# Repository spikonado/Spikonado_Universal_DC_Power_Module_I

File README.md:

# Spikonado Universal DC Power Module I

The [Spikonado Universal DC Power Module I](https://spikonado.com/product/spikonado-universal-dc-power-module-i) is a versatile and high-current buck converter designed to power your most demanding electronics projects. It efficiently (92.7%) converts a wide **13-24** DC input into three stable, dedicated outputs:

- **12V @ 4A**
- **5V @ 10A**
- **3.3V @ 8A**

This module is perfect for robotics, embedded systems, single-board computers (SBCs), custom test jigs, and any application requiring reliable multi-voltage power.<br>
Further enhancing its flexibility, the board includes USB-C and USB-A outputs.<br>
What's more, we have also included EN and PG pins through which you can control the board using a microcontroller and also attach a switch to the board.

The board also includes the following protections:

1. Over Current Limit (OCL) - Protects the board from overloads by limiting the output current.
2. Undervoltage Lockout (UVLO) - When the input voltage on VIN falls below the required voltage, the particular voltage output shuts off.
3. Thermal Shutdown - When any of the buck converter ICs included on the board get too hot, the particular voltage output shuts off.
4. Undervoltage and Overvoltage Protection (UVP & OVP) (Not included for 12V output) - When the output voltage falls too low or goes too high than the desired voltage, the output is discharged and latched.

## 📂 About this Repository

This repository is your central hub for all information, design files, and resources related to the Spikonado Universal DC Power Module I. Our aim is to provide everything you need to understand, use, and even build upon this product.

You'll find:

- `docs/`: Comprehensive documentation, including datasheets, specifications, and user guides.
- `hardware_design/`: Complete KiCad project design files – schematics and PCB layout for the board.

## Accessing the Documentation

The `docs/` directory contains the source files for our comprehensive product documentation. For the best reading experience, with all formatting and interactive elements correctly rendered, please view the built version on our [website](https://docs.spikonado.com/Spikonado_Universal_DC_Power_Module_I).

While you can browse the raw files in the `docs/` directory on GitHub, they are primarily intended for those contributing to the documentation or exploring its source structure.

## 🤝 Contributing

Contributions, issues, and feature requests are welcome! Feel free to check existing issues or open a new one.

## 📄 License

This product is open source!

Please review the following files for license information:

- `hardware_design/LICENSE.md`

If you have any questions or concerns related to licensing, please email support at support@spikonado.com.

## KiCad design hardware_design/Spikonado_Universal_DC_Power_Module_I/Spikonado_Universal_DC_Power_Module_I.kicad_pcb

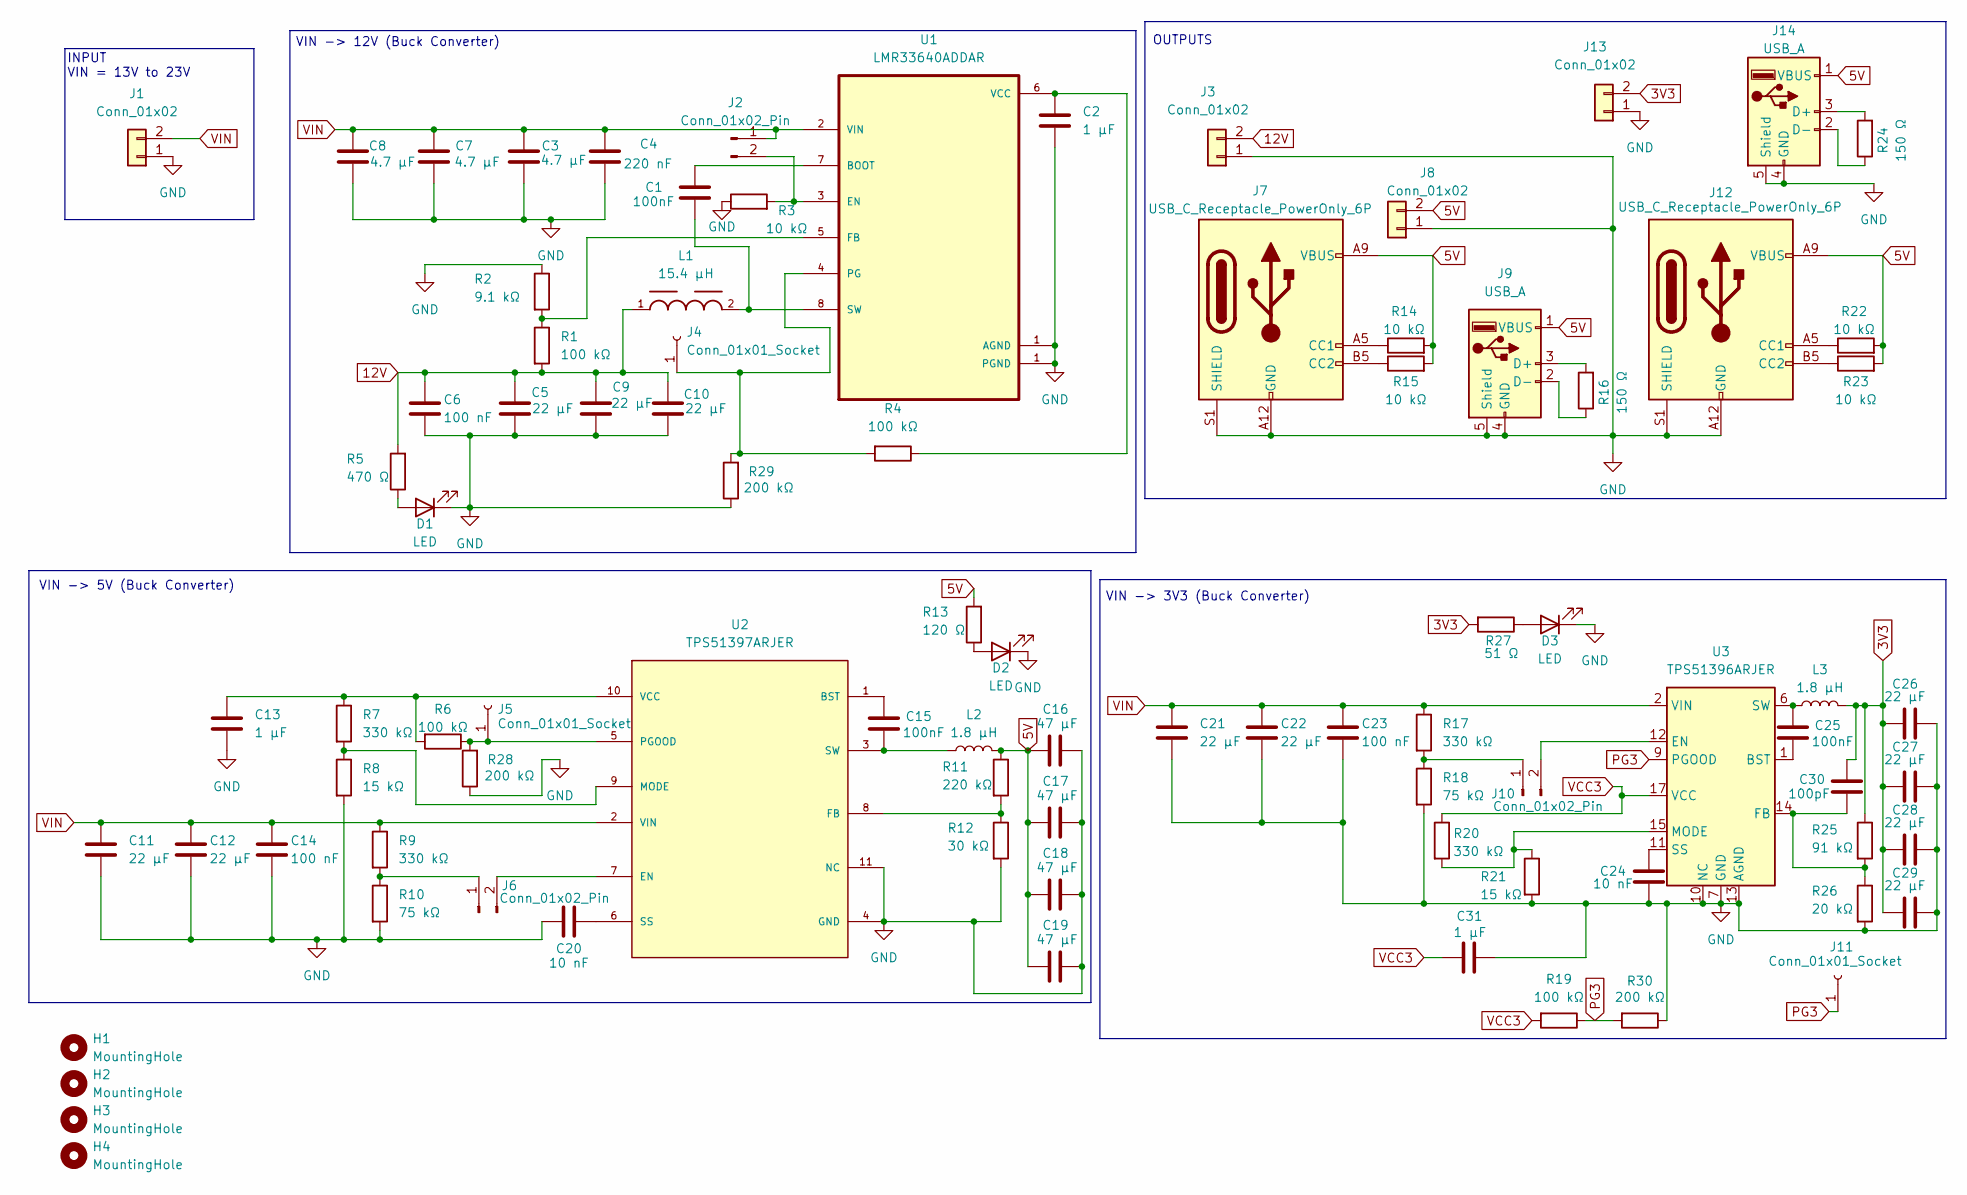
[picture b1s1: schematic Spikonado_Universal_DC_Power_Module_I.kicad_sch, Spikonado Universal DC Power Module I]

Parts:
C1, C15, C25: 100nF; C_0805_2012Metric
C2, C13, C31: 1 μF; C_0402_1005Metric
C3, C7, C8: 4.7 μF; C_1206_3216Metric
C4: 220 nF; C_0805_2012Metric
C5, C9, C10: 22 μF; C_0805_2012Metric
C6, C14, C23: 100 nF; C_0805_2012Metric
C11, C12, C21, C22, C26, C27, C28, C29: 22 μF; C_1206_3216Metric
C16, C17, C18, C19: 47 μF; C_1206_3216Metric
C20, C24: 10 nF; C_0805_2012Metric
C30: 100pF; C_0805_2012Metric
D1, D2, D3: LED; LED_0603_1608Metric
H1, H2, H3, H4: MountingHole; MountingHole_3.2mm_M3
J1, J3, J8, J13: Conn_01x02; TerminalBlock_MaiXu_MX126-5.0-02P_1x02_P5.00mm
J2, J6, J10: Conn_01x02_Pin; PinHeader_1x02_P2.54mm_Vertical
J4, J5, J11: Conn_01x01_Socket; PinSocket_1x01_P2.54mm_Vertical
J7, J12: USB_C_Receptacle_PowerOnly_6P; USB_C_Receptacle_GCT_USB4125-xx-x_6P_TopMnt_Horizontal
J9, J14: USB_A; USB_A_Connfly_DS1095
L1: 15.4 µH; WE-HCI_1365
L2, L3: 1.8 μH; IND_IHLP_5050_FD_VIS
R1, R4, R6, R19: 100 kΩ; R_0805_2012Metric
R2: 9.1 kΩ; C_0603_1608Metric
R3, R14, R15, R22, R23: 10 kΩ; R_0805_2012Metric
R5: 470 Ω; R_0805_2012Metric
R7, R9, R17, R20: 330 kΩ; R_0603_1608Metric
R8, R21: 15 kΩ; R_0603_1608Metric
R10, R18: 75 kΩ; R_0603_1608Metric
R11: 220 kΩ; R_0805_2012Metric
R12: 30 kΩ; R_0805_2012Metric
R13: 120 Ω; R_0805_2012Metric
R16, R24: 150 Ω; R_0805_2012Metric
R25: 91 kΩ; R_0603_1608Metric
R26: 20 kΩ; R_0603_1608Metric
R27: 51 Ω; R_0805_2012Metric
R28, R29, R30: 200 kΩ; R_0805_2012Metric
U1: LMR33640ADDAR; VREG_LM5017MR_NOPB
U2: TPS51397ARJER; RJE0020B-MFG
U3: TPS51396ARJER; Texas_RJE0020A_VQFN-20-1EP_3x3mm_P0.45mm_EP0.675x0.76mm_The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

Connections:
3V3: C26.2, C27.2, C28.2, C29.2, C30.1, J13.2, L3.2, R25.1, R27.2
5V: C16.1, C17.1, C18.1, C19.1, J7.A9 (VBUS), J7.B9 (VBUS), J8.2, J9.1 (VBUS), J12.A9 (VBUS), J12.B9 (VBUS), J14.1 (VBUS), L2.2, R11.1, R13.2, R14.2, R15.2, R22.2, R23.2
12V: C5.2, C6.1, C9.1, C10.2, J3.2, L1.1, R1.2, R5.2
GND: C2.2, C3.1, C4.2, C5.1, C6.2, C7.1, C8.1, C9.2, C10.1, C11.1, C12.1, C13.2, C14.2, C16.2, C17.2, C18.2, C19.2, C20.2, C21.1, C22.1, C23.2, C24.2, C26.1, C27.1, C28.1, C29.1, C31.2, D1.1 (K), D2.1 (K), D3.1 (K), J1.1, J3.1, J7.A12 (GND), J7.B12 (GND), J7.S1 (SHIELD), J8.1, J9.4 (GND), J9.5 (Shield), J12.A12 (GND), J12.B12 (GND), J12.S1 (SHIELD), J13.1, J14.4 (GND), J14.5 (Shield), R2.1, R3.1, R8.2, R10.2, R12.2, R18.2, R21.2, R26.2, R28.1, R29.1, R30.1, U1.1 (PGND), U2.4 (GND), U2.11 (NC), U3.7 (GND), U3.8 (GND), U3.10 (NC), U3.13 (AGND), U3.16 (NC), U3.18 (GND), U3.21 (GND)
unnamed: C25.2, L3.1, U3.6 (SW), U3.19 (SW), U3.20 (SW)
unnamed: D1.2 (A), R5.1
unnamed: D2.2 (A), R13.1
unnamed: D3.2 (A), R27.1
unnamed: J2.2, R3.2, U1.3 (EN)
unnamed: J4.1, R4.2, R29.2, U1.4 (PG)
unnamed: J5.1, R6.1, R28.2, U2.5 (PGOOD)
unnamed: J6.1, R9.2, R10.1
unnamed: J6.2, U2.7 (EN)
unnamed: J7.A5 (CC1), R14.1
unnamed: J7.B5 (CC2), R15.1
unnamed: J9.3 (D+), R16.2
unnamed: J9.2 (D-), R16.1
unnamed: J10.1, R17.2, R18.1
unnamed: J10.2, U3.12 (EN)
unnamed: J12.A5 (CC1), R22.1
unnamed: J12.B5 (CC2), R23.1
unnamed: J14.3 (D+), R24.2
unnamed: J14.2 (D-), R24.1
unnamed: C1.1, U1.7 (BOOT)
unnamed: R1.1, R2.2, U1.5 (FB)
unnamed: C1.2, L1.2, U1.8 (SW)
unnamed: C2.1, R4.1, U1.6 (VCC)
unnamed: C15.2, U2.1 (BST)
unnamed: R11.2, R12.1, U2.8 (FB)
unnamed: R7.2, R8.1, U2.9 (MODE)
unnamed: C20.1, U2.6 (SS)
unnamed: C15.1, L2.1, U2.3 (SW)
unnamed: C13.1, R6.2, R7.1, U2.10 (VCC)
unnamed: C25.1, U3.1 (BST)
unnamed: C30.2, R25.2, R26.1, U3.14 (FB)
unnamed: R20.2, R21.1, U3.15 (MODE)
unnamed: C24.1, U3.11 (SS)
PG3: J11.1, R19.1, R30.2, U3.9 (PGOOD)
VCC3: C31.1, R19.2, R20.1, U3.17 (VCC)
VIN: C3.2, C4.1, C7.2, C8.2, C11.2, C12.2, C14.1, C21.2, C22.2, C23.1, J1.2, J2.1, R9.1, R17.1, U1.2 (VIN), U2.2 (VIN), U3.2 (VIN), U3.3 (VIN), U3.4 (VIN), U3.5 (VIN)

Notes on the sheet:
VIN -> 12V (Buck Converter)
OUTPUTS
VIN -> 3V3 (Buck Converter)
VIN -> 5V (Buck Converter)
INPUT VIN = 13V to 23V

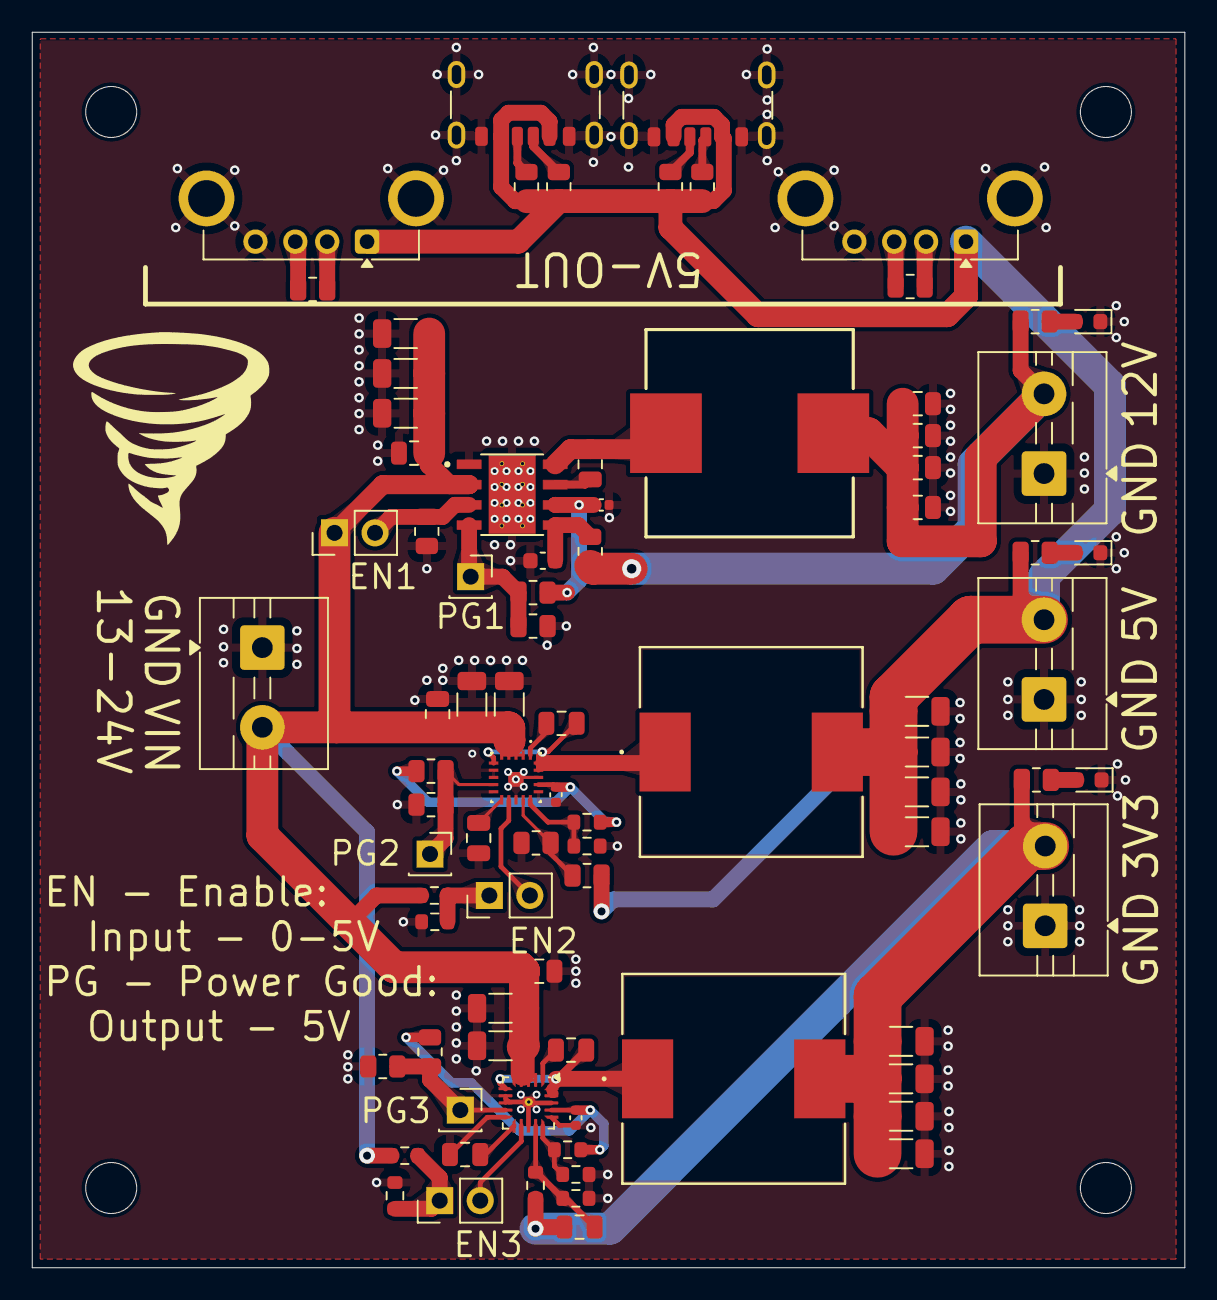
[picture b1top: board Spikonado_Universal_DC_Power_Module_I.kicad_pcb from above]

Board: 4 copper layers, 72.3 x 77.5 mm, 88 parts (0 on the bottom side), 40 nets.

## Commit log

2025-06-02 Deployed 85c3c0c with MkDocs version: 1.5.3
2025-06-02 Fix 3D model path
2025-06-02 Deployed 6e2f0b9 with MkDocs version: 1.5.3
2025-06-02 Fix link to built docs
2025-06-04 Update specifications documentation
2025-06-04 Deployed bf7cd6c with MkDocs version: 1.5.3

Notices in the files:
hardware_design/Spikonado_Universal_DC_Power_Module_I/Spikonado_Universal_DC_Power_Module_I.kicad_pcb:
To view a copy of this license, visit https://creativecommons.org/licenses/by-sa/4.0
Spikonado hardware design is licensed under CC BY-SA 4.0.
